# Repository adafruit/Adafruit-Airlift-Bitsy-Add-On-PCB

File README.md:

## Adafruit Adafruit Airlift Bitsy Add-On PCB

<a href="http://www.adafruit.com/products/4363"><br/>
Click here to purchase one from the Adafruit shop</a>

PCB files for the Adafruit Adafruit Airlift Bitsy Add-On. 

Format is EagleCAD schematic and board layout
* https://www.adafruit.com/product/4363

### Description

Give your ItsyBitsy project a lift with the Adafruit AirLift Bitsy Add-On; - it's the first add-on for the ItsyBitsy and it lets you use the powerful ESP32 as a WiFi co-processor. You probably have your favorite ItsyBitsy (like the [ItsyBitsy M4](https://www.adafruit.com/product/3800)) that comes with its own set of awesome peripherals and lots of libraries. But it doesn't have WiFi built in! So let's give that chip a best friend, the ESP32. This chip can handle all the heavy lifting of connecting to a WiFi network and transferring data from a site, even if its using the latest TLS/SSL encryption (it has root certificates pre-burned in).

### License

Adafruit invests time and resources providing this open source design, please support Adafruit and open-source hardware by purchasing products from [Adafruit](https://www.adafruit.com)!

Designed by Bryan Siepert for Adafruit Industries.

Creative Commons Attribution/Share-Alike, all text above must be included in any redistribution. 
See license.txt for additional details.

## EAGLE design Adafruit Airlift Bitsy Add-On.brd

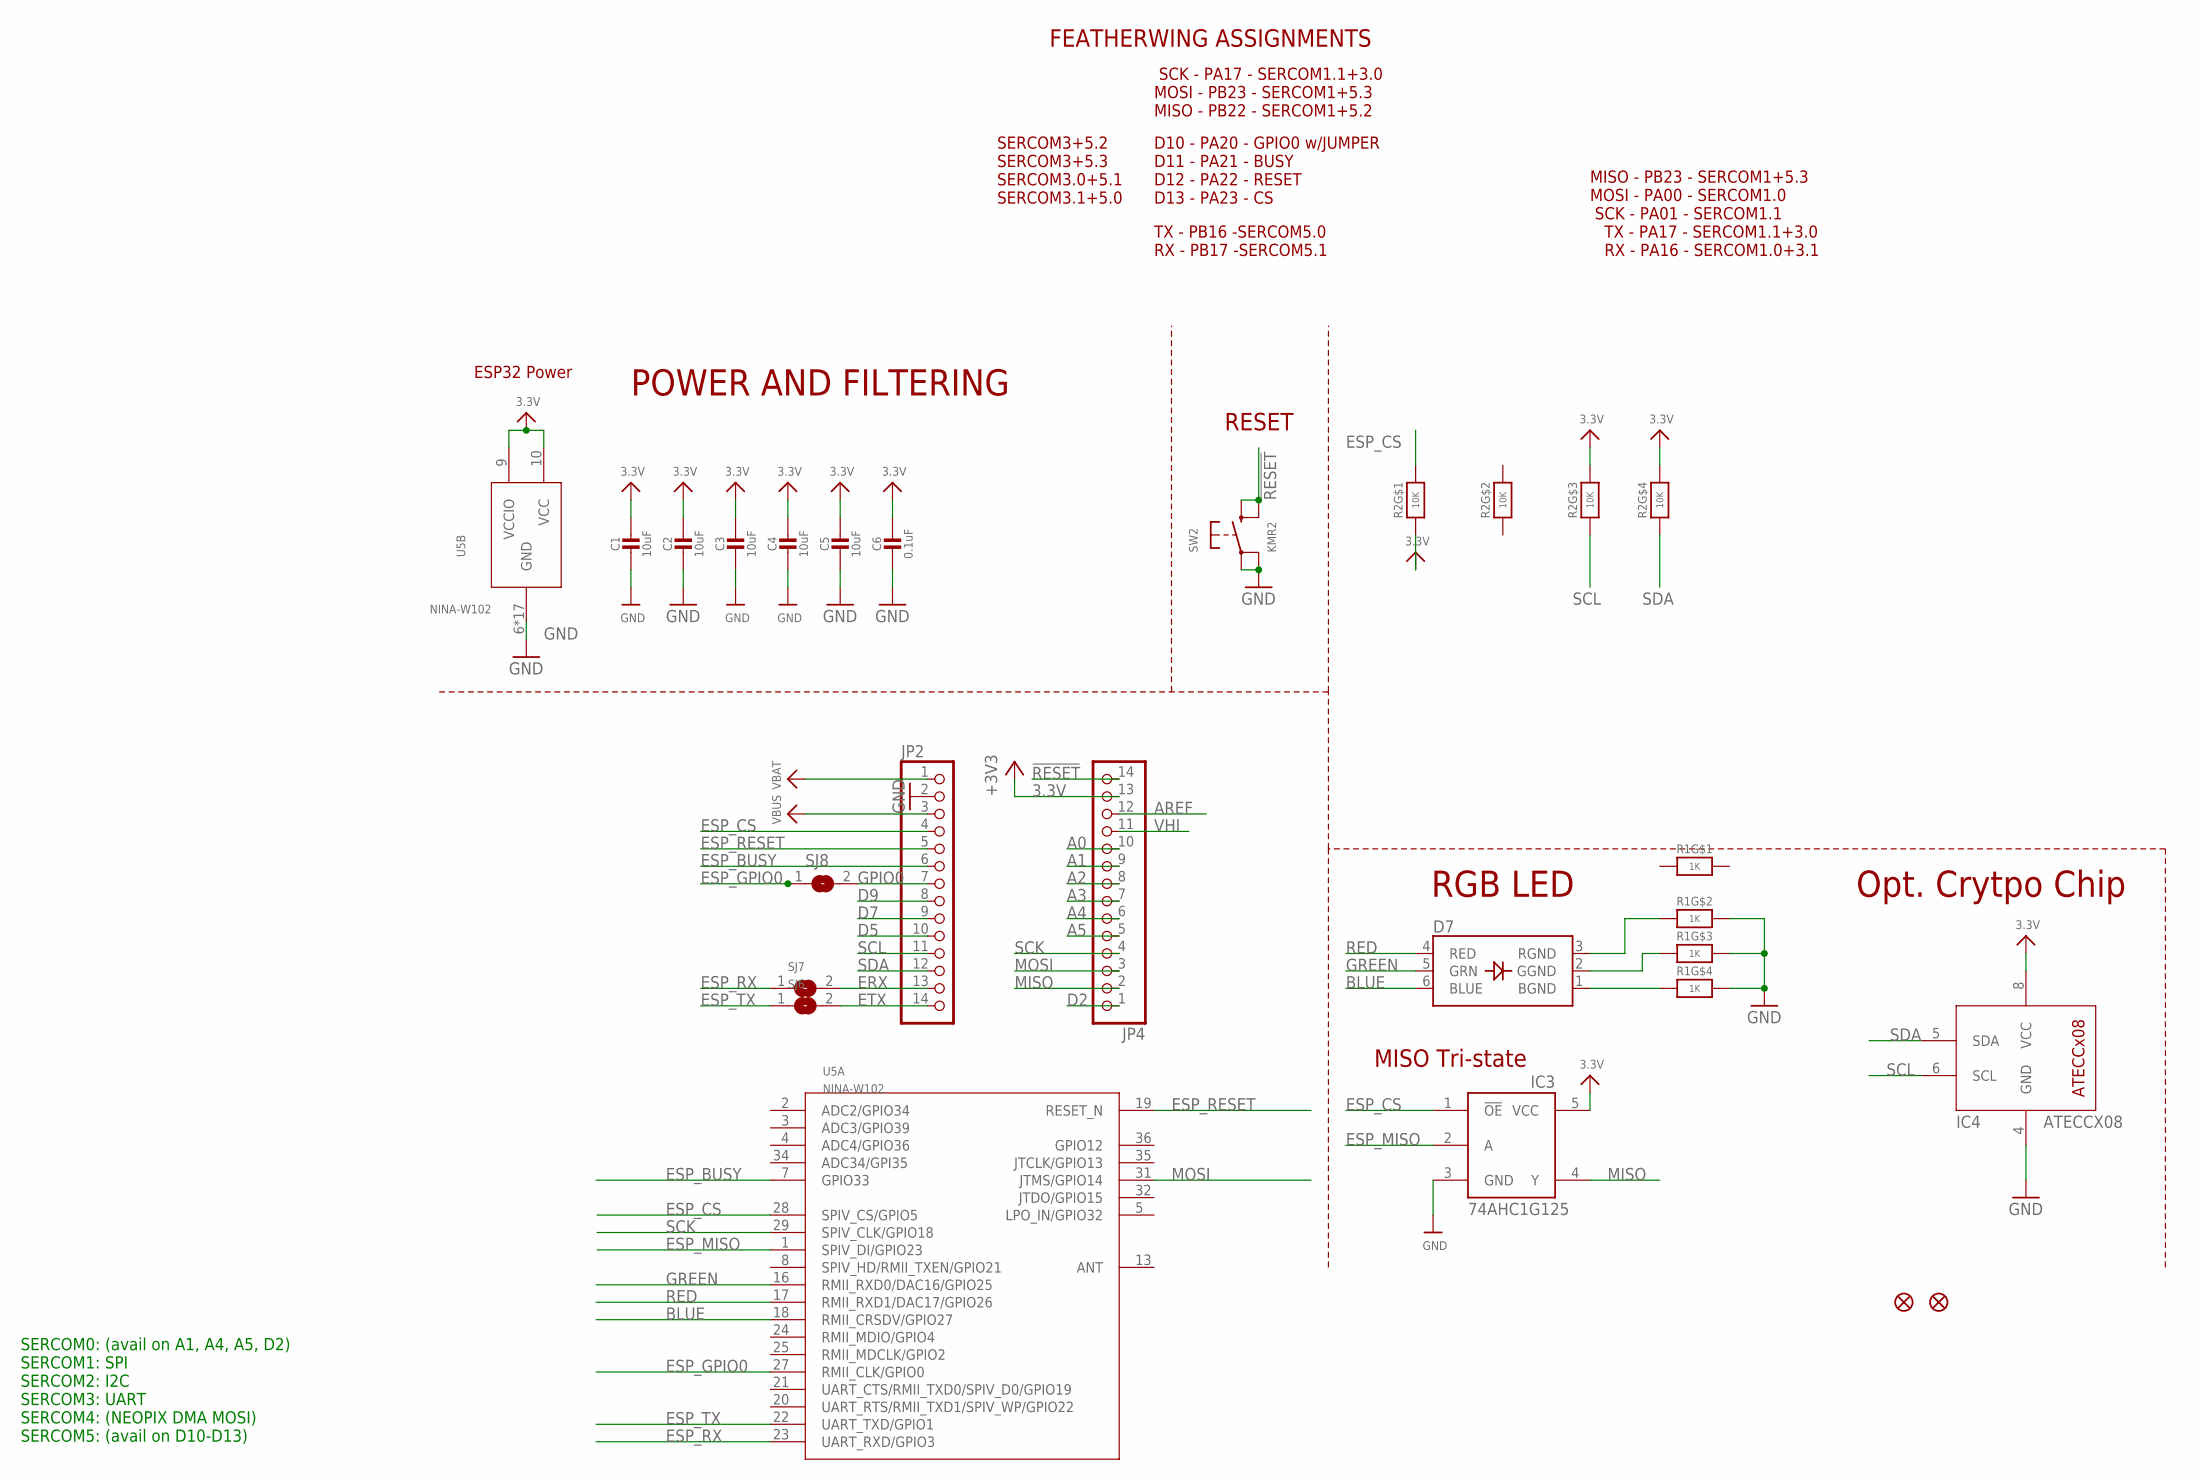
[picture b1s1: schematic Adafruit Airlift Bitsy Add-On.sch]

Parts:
C1, C2, C3, C4, C5: 10uF; 0805-NO
C6: 0.1uF; 0603-NO
D7: LED_RGB_PLCC63535; RGBLED_3535_PLCC6
IC3: 74AHC1G125; SOT23-5L
IC4: ATECCX08; SOIC8_150MIL
JP2, JP4: HEADER-1X14; 1X14_ROUND70
R1: 1K; RESPACK_4X0603_NO
R2: 10K; RESPACK_4X0603_NO
SJ6, SJ7, SJ8: SOLDERJUMPER; SOLDERJUMPER_ARROW_NOPASTE
SW2: KMR2; BTN_KMR2_4.6X2.8
U5: NINA-W102; ARDUINO-UCS&SOCS_NINA-W1X
U$34, U$35: FIDUCIAL_1MM

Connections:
3.3V: C1.1, C2.1, C3.1, C4.1, C5.1, C6.1, IC3.5 (VCC), IC4.8 (VCC), JP4.13, R2.1, R2.5 (2), R2.6 (2), U5.9 (VCCIO), U5.10 (VCC)
!RESET: JP4.14, SW2.B (S), SW2.B' (S1)
A0: JP4.10
A1: JP4.9
A2: JP4.8
A3: JP4.7
A4: JP4.6
A5: JP4.5
AREF: JP4.12
BLUE: D7.6 (BLUE), U5.18 (RMII_CRSDV/GPIO27)
D2: JP4.1
D5: JP2.10
D7: JP2.9
D9: JP2.8
ERX: JP2.13, SJ7.2
ESP_BUSY: JP2.6, U5.7 (GPIO33)
ESP_CS: IC3.1 (!OE), JP2.4, R2.8 (2), U5.28 (SPIV_CS/GPIO5)
ESP_GPIO0: SJ8.1, U5.27 (RMII_CLK/GPIO0)
ESP_MISO: IC3.2 (A), U5.1 (SPIV_DI/GPIO23)
ESP_RESET: JP2.5, U5.19 (RESET_N)
ESP_RX: SJ7.1, U5.23 (UART_RXD/GPIO3)
ESP_TX: SJ6.1, U5.22 (UART_TXD/GPIO1)
ETX: JP2.14, SJ6.2
GND: C1.2, C2.2, C3.2, C4.2, C5.2, C6.2, IC3.3 (GND), IC4.4 (GND), JP2.2, R1.5 (2), R1.6 (2), R1.7 (2), SW2.A, SW2.A' (P1), U5.6 (GND), U5.12 (GND), U5.14 (GND), U5.26 (GND), U5.30 (GND), U5.GND@1 (GND), U5.GND@2 (GND), U5.GND@3 (GND), U5.GND@4 (GND), U5.GND@5 (GND), U5.GND@6 (GND), U5.GND@7 (GND), U5.GND@8 (GND), U5.GND@9 (GND), U5.GND@10 (GND), U5.GND@11 (GND), U5.GND@12 (GND)
GPIO0: JP2.7, SJ8.2
GREEN: D7.5 (GRN), U5.16 (RMII_RXD0/DAC16/GPIO25)
MISO: IC3.4 (Y), JP4.2
MOSI: JP4.3, U5.31 (JTMS/GPIO14)
unnamed: D7.1 (BGND), R1.4 (1)
unnamed: D7.2 (GGND), R1.3 (1)
unnamed: D7.3 (RGND), R1.2 (1)
RED: D7.4 (RED), U5.17 (RMII_RXD1/DAC17/GPIO26)
SCK: JP4.4, U5.29 (SPIV_CLK/GPIO18)
SCL: IC4.6 (SCL), JP2.11, R2.3 (1)
SDA: IC4.5 (SDA), JP2.12, R2.4 (1)
VBAT: JP2.1
VBUS: JP2.3
VHI: JP4.11

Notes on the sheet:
SERCOM0: (avail on A1, A4, A5, D2) SERCOM1: SPI SERCOM2: I2C SERCOM3: UART SERCOM4: (NEOPIX DMA MOSI) SERCOM5: (avail on D10-D13)
POWER AND FILTERING
RESET
RGB LED
Opt. Crytpo Chip
MISO Tri-state
D10 - PA20 - GPIO0 w/JUMPER D11 - PA21 - BUSY D12 - PA22 - RESET D13 - PA23 - CS
TX - PB16 -SERCOM5.0 RX - PB17 -SERCOM5.1
SERCOM3+5.2 SERCOM3+5.3 SERCOM3.0+5.1 SERCOM3.1+5.0
SCK - PA17 - SERCOM1.1+3.0 MOSI - PB23 - SERCOM1+5.3 MISO - PB22 - SERCOM1+5.2
FEATHERWING ASSIGNMENTS
MISO - PB23 - SERCOM1+5.3 MOSI - PA00 - SERCOM1.0 SCK - PA01 - SERCOM1.1 TX - PA17 - SERCOM1.1+3.0 RX - PA16 - SERCOM1.0+3.1
ESP32 Power

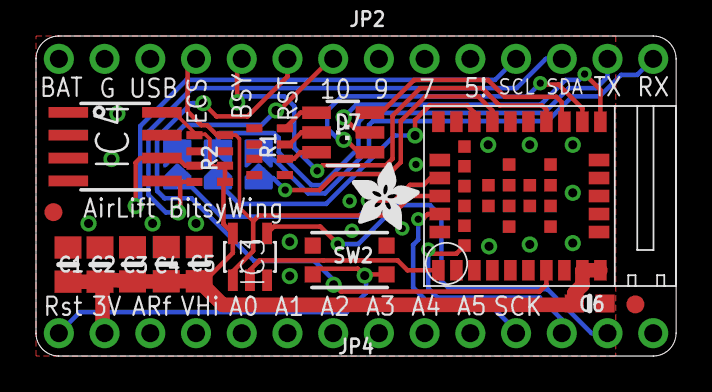
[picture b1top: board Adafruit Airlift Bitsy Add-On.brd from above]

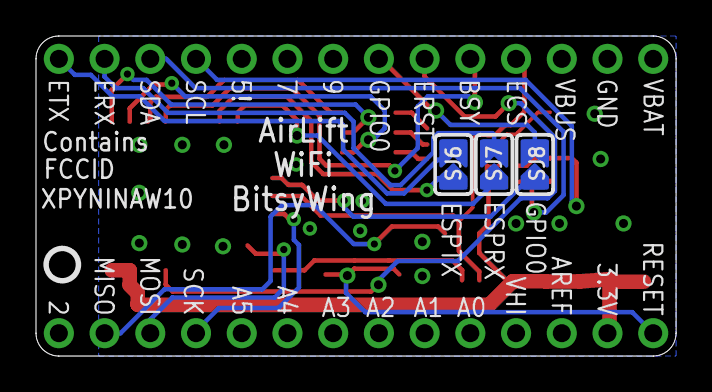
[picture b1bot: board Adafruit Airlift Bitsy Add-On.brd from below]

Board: 2 copper layers, 35.6 x 17.8 mm, 22 parts (4 on the bottom side), 24 nets.

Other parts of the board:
U$6: PCBFEAT-REV-040
U$62: ADAFRUIT_3.5MM

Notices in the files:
parts and their libraries:
microbuilder: This work is placed in the public domain, and may be freely used for commercial and non-commercial work with the following conditions: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
SparkFun-Aesthetics: Licensing: CC v3.0 Share-Alike You are welcome to use this library for commercial purposes.
